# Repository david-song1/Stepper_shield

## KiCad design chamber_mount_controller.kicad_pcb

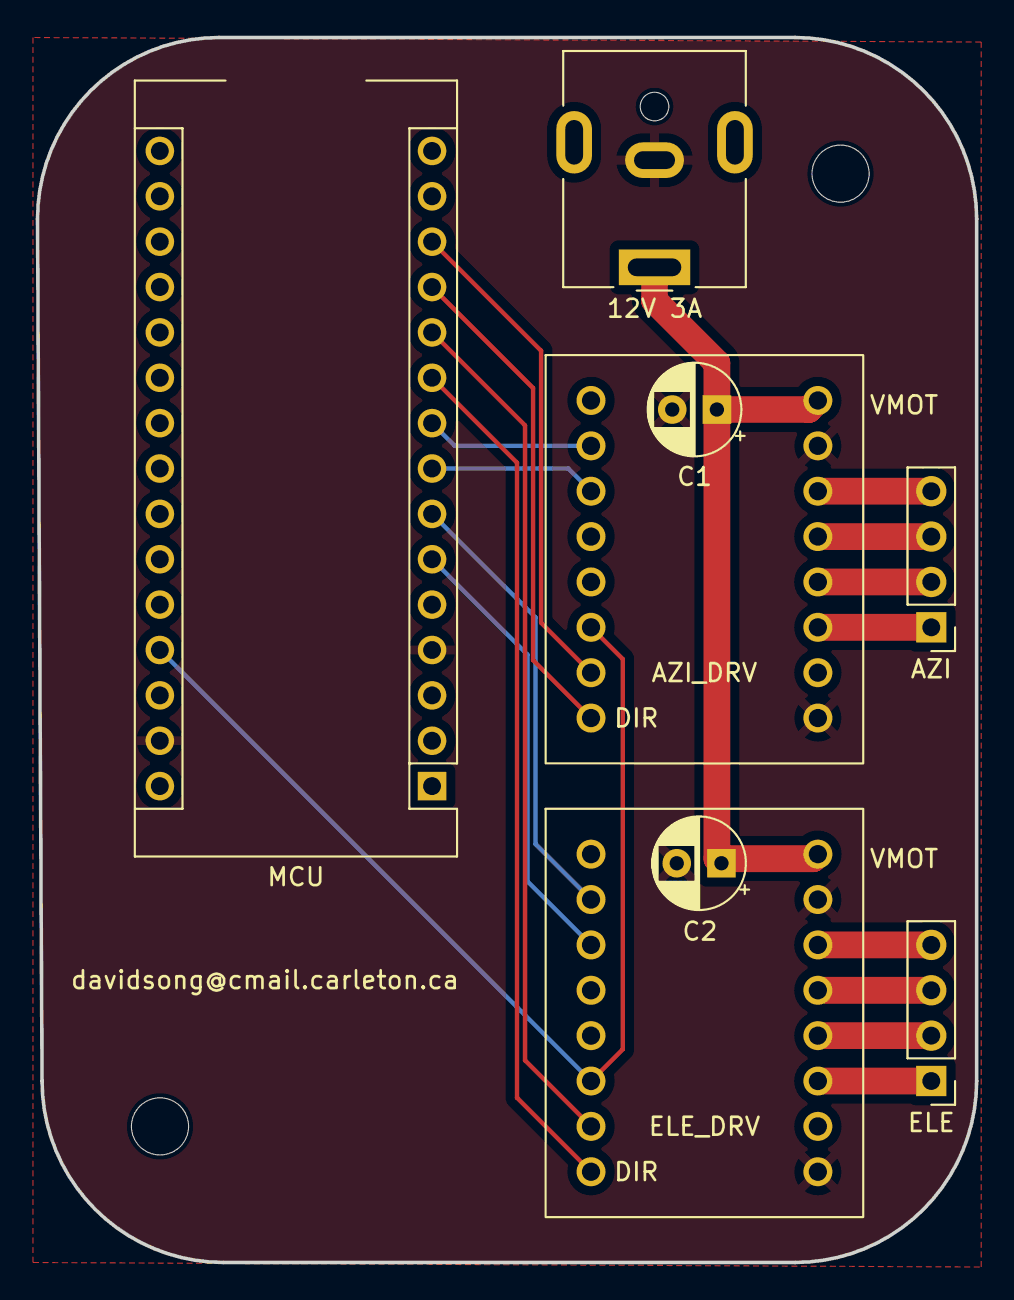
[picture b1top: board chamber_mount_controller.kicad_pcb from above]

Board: 2 copper layers, 52.6 x 68.6 mm, 8 parts (0 on the bottom side), 19 nets.

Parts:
12V 3A: Conn_01x02; BarrelJack_CUI_PJ-063AH_Horizontal
AZI: Conn_01x04; PinHeader_1x04_P2.54mm_Vertical
AZI_DRV: MP6500; mp6500
C1, C2: C_Polarized_Small; CP_Radial_D5.0mm_P2.50mm
ELE: Conn_01x04; PinHeader_1x04_P2.54mm_Vertical
ELE_DRV: MP6500; mp6500
MCU: Arduino_Uno_Shield; Arduino_Nano

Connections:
+5V: AZI_DRV.6 (~sleep), ELE_DRV.6 (~sleep), MCU.27 (+5V)
GND: 12V 3A.2, AZI_DRV.10 (GND), AZI_DRV.16 (GND), C1.2, C2.2, ELE_DRV.10 (GND), ELE_DRV.16 (GND), MCU.4 (GND), MCU.29 (GND)
unnamed: ELE.1, ELE_DRV.14 (A1)
unnamed: ELE.2, ELE_DRV.13 (A2)
unnamed: ELE.3, ELE_DRV.12 (B1)
unnamed: ELE.4, ELE_DRV.11 (B2)
unnamed: AZI.1, AZI_DRV.14 (A1)
unnamed: AZI.2, AZI_DRV.13 (A2)
unnamed: AZI.3, AZI_DRV.12 (B1)
unnamed: AZI.4, AZI_DRV.11 (B2)
unnamed: ELE_DRV.8 (dir), MCU.10 (D7)
unnamed: ELE_DRV.2 (ms1), MCU.7 (D4)
unnamed: ELE_DRV.3 (ms2), MCU.6 (D3)
unnamed: ELE_DRV.7 (step), MCU.11 (D8)
unnamed: AZI_DRV.8 (dir), MCU.12 (D9)
unnamed: AZI_DRV.2 (ms1), MCU.9 (D6)
unnamed: AZI_DRV.3 (ms2), MCU.8 (D5)
unnamed: AZI_DRV.7 (step), MCU.13 (D10)
VCC: 12V 3A.1, AZI_DRV.9 (VMOT), C1.1, C2.1, ELE_DRV.9 (VMOT)

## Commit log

2023-02-21 added gitignore for backup files
2023-02-22 updated files
2023-02-23 Redid layout for arduino nano, added DC barrel jack
2023-02-24 Re-routed traces to remove need for microstepping DIP switches
